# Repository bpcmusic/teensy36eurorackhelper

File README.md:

# teensy36eurorackhelper
little board to help the teensy 3.6 boot in eurorack modules

---

Mount this little fellow underneath your Teensy 3.6 if you are having trouble booting when mounted in place of a Teensy 3.2 in a Eurorack module. The symptom is that the module never executes your code when booted without USB power.

This board adds a voltage supervisor that delays the start of the Teensy (via the Reset pin) until there is adequate power. It was designed to fit on the bottom of the board in an area that would not be populated for a Teensy 3.2.

<a href="https://oshpark.com/shared_projects/2kwylotu"></img></a>

You can always use Eagle to create your own Gerbers and select your own fab house.

## Project BOM:

* 1 x MIC803 (MIC803-26D2VM3-TR
): http://www.mouser.com/search/ProductDetail.aspx?r=998%2dMIC803%2d26D2VM3TR

* 1 x 100k 1% 0603 Resistor (71-CRCW0603100KFKEAC
): https://www.mouser.com/ProductDetail/71-CRCW0603100KFKEAC?r=71-CRCW0603100KFKEAC

* 2 x 1x4 Male Headers (appropriate to your installation)

* 1 x 1x5 Male Header (appropriate to your installation)

---

More details are in this thread over at the Teensy forum: 

https://forum.pjrc.com/threads/44704-Boot-on-Power-Up-Problem-with-three-T3-6s

Thanks to everyone there (especially neutron7) for finding the solution. All I did was panel the thing up. Saved my bacon on a project. :)

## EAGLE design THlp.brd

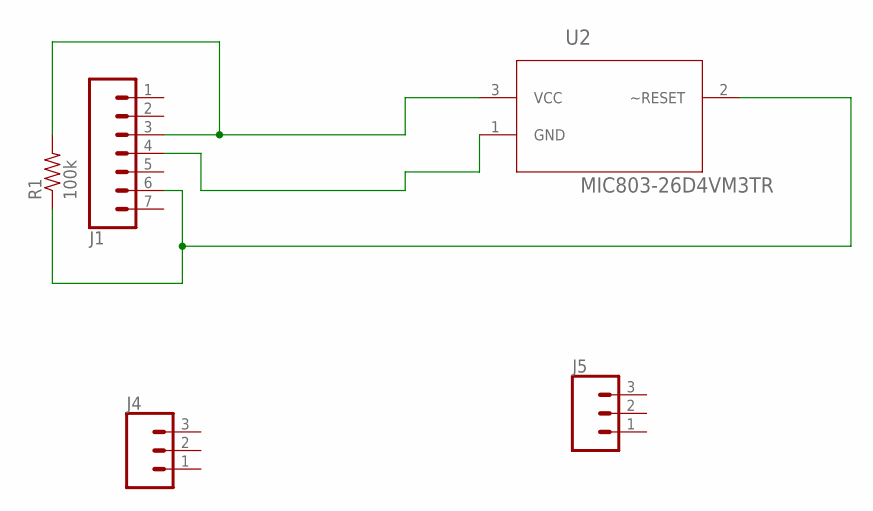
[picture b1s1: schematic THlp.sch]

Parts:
J1: CONN_07; 1X07
J4, J5: CONN_03PTH; 1X03
R1: 100k; 0603-RES
U2: MIC803-26D4VM3TR; SOT95P232X110-3N

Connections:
unnamed: J1.4, U2.1 (GND)
unnamed: J1.3, R1.2, U2.3 (VCC)
unnamed: J1.6, R1.1, U2.2 (~RESET)

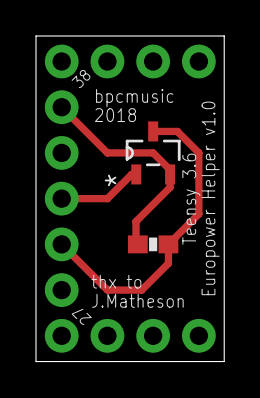
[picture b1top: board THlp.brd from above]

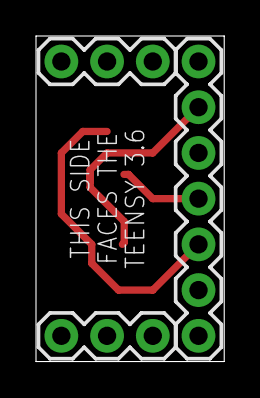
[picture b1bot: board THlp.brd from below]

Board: 2 copper layers, 10.5 x 18.1 mm, 5 parts (3 on the bottom side), 3 nets.

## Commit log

2018-02-11 initial commit of files
2018-02-11 added images to read.me
2018-02-11 added OSHPark link
2018-02-11 added BOM

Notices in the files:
parts and their libraries:
SparkFun-Connectors: Licensing: Creative Commons ShareAlike 4.0 International - https://creativecommons.org/licenses/by-sa/4.0
